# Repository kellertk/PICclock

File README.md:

# PICclock

Variable-frequency clock generator using PIC16F18344 hardware NCO.

See [src/README.md](src/README.md) and [hardware/README.md](hardware/README.md) for details.

## Features

- 1 Hz to 1 MHz output with 50% duty cycle
- Hardware NCO for 12+ Hz (zero CPU overhead)
- Software timing for 1-11 Hz
- Logarithmic frequency sweep via potentiometer
- Step mode for single pulses

## Building

1. Run the configure script:
   - Windows: `.\configure.ps1`
   - Linux/macOS: `./configure`

2. Build: `make`

3. Flash: `make flash`

## Requirements

- Microchip XC8 compiler
- MPLAB X IDE (for IPE and DFP)
- PICkit 5 (or compatible programmer)
- PIC16F1xxxx_DFP device family pack

## License

This project is intentionally available under a restrictive license: CC BY-NC-SA.
Commercial use of this work is not permitted without prior agreement. Please contact
me if you need alternate licensing terms. See [LICENSE.txt](LICENSE.txt) for details.

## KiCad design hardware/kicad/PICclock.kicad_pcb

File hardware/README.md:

# PICclock Hardware

## Overview

**Architecture:**
```
                          ACTIVE CLOCK OUTPUT
                                  ^
                                  |
                          +-------+-------+
                          |U3: EL7232CNZ  |
                          | Line Driver   |
                          +-------+-------+
                                  |
                          +-------+-------+
                          |U2: 74HC00     |
                          | (VAR/HS MUX)  |
                          +---+-------+---+
                              |       |
                +-------------+       +-------------+
                |                                   |
        VARIABLE CLOCK                        HIGH-SPEED
        (PIC RB6 NCO output)                  OSCILLATOR
                |                                (Y2)
          +-----+-----+
          |   PIC     |
          |   U1      |
          +-----+-----+
           |  |  |  |  |
       [POT][BTN][SW1][SW2]
```

**Clock Modes:**
- **Variable**: Hybrid NCO/software clock from PIC (1 Hz - 1 MHz), 50% duty cycle
- **Step**: Single pulse per button press (handled by PIC, debounced in software)
- **High-Speed**: External oscillator bypass

**Frequency Control:** PIC reads potentiometer via ADC. Hardware NCO generates clock for 12 Hz - 1 MHz; software timing handles 1 Hz - 11 Hz. Frequency accuracy inherits PIC crystal stability (typically ±50 ppm).

**Output Driver:** EL7232CNZ line driver buffers clock output.

**Variable Frequency Range:** 1 Hz to 1 MHz (hybrid NCO/software, 50% duty cycle)

---

## Components

### ICs

| Ref | Part | Function |
|-----|------|----------|
| U1 | PIC16F18344-I/P | Clock generation (NCO + software timing) |
| U2 | 74HC00 | Quad NAND (var/HS mux) |
| U3 | EL7232CNZ | Line driver |

### Oscillators

| Ref | Part | Function |
|-----|------|----------|
| Y1 | 24 MHz crystal | PIC clock |
| Y2 | Oscillator module (w/enable) | High-speed clock (user-selected frequency) |

### Switches & Controls

| Ref | Part | Function |
|-----|------|----------|
| SW1 | SPDT slide | Variable/Step select |
| SW2 | SPDT slide | Variable/High-Speed select |
| SW3 | Pushbutton (NO) | Step pulse trigger |
| VR1 | 10K pot | Frequency control |

### Passive Components

| Ref | Value | Function |
|-----|-------|----------|
| C1 | 10nF | U1 bypass |
| C2 | 100nF | U1 bypass |
| C3, C4 | 22pF | Y1 load caps |
| C5 | 10nF | U2 bypass |
| C6 | 100nF | U2 bypass |
| C7 | 10nF | U3 bypass |
| C8 | 100nF | U3 bypass |
| R1 | 10K | MCLR pull-up |
| R2 | 330Ω | Debug LED current limit |
| R3 | 47Ω | Clock output series resistor |
| R4 | 470Ω | Clock LED current limit |
| LED1 | LED | Debug indicator |
| LED2 | LED | Clock indicator |

---

## Signal Reference

| Signal | Description |
|--------|-------------|
| VAR_CLK | Variable clock from PIC (RB6 NCO1), active low |
| HS_CLK | High-speed external oscillator |
| STEP_SEL | Step mode select (SW1, active low = step) |
| HALT_SEL | High-speed mode select (SW2, active low = high-speed) |
| CLK_OUT | Final clock output (from U3) |

---

## U1: PIC16F18344-I/P (DIP-20)

```
                    +------------+
              VDD --|1         20|-- VSS (GND)
         RA5/OSC1 --|2         19|-- RA0/AN0 <-- VR1 (POT)
         RA4/OSC2 --|3         18|-- RA1/ICSPCLK
     MCLR/VPP/RA3 --|4         17|-- RA2 -x
DEBUG_LED <-- RC5 --|5         16|-- RC0 -x
      SW3 --> RC4 --|6         15|-- RC1 -x
      SW1 --> RC3 --|7         14|-- RC2 -x
      SW2 --> RC6 --|8         13|-- RB4 -x
           x- RC7 --|9         12|-- RB5 -x
           x- RB7 --|10        11|-- RB6 --> VAR_CLK
                    +------------+
```

| Pin | Name | Signal | To |
|-----|------|--------|----|  
| 1 | VDD | +5V | +5V, J1-2 |
| 2 | RA5/OSC1 | XTAL | Y1, C1 |
| 3 | RA4/OSC2 | XTAL | Y1, C2 |
| 4 | MCLR/VPP/RA3 | MCLR | +5V via R1, J1-1 |
| 5 | RC5 | DEBUG_LED | LED, current limit resistor to GND |
| 6 | RC4 | STEP_BTN | SW3 (internal pull-up) |
| 7 | RC3 | STEP_SEL | SW1 common |
| 8 | RC6 | HALT_SEL | SW2 common |
| 9 | RC7 | - | nc |
| 10 | RB7 | - | nc |
| 11 | RB6 | VAR_CLK | U2-4 (mux input) |
| 12 | RB5 | - | nc |
| 13 | RB4 | - | nc |
| 14 | RC2 | - | nc |
| 15 | RC1 | - | nc |
| 16 | RC0 | - | nc |
| 17 | RA2 | - | nc |
| 18 | RA1 | ICSPCLK | J1-5 |
| 19 | RA0/AN0 | POT | VR1 wiper, J1-4 (ICSPDAT) |
| 20 | VSS | GND | GND, J1-3 |

---

## U2: 74HC00

```
74HC00 (DIP-14)
       +-------+
    1A-|1    14|-VCC
    1B-|2    13|-4B
    1Y-|3    12|-4A
    2A-|4    11|-4Y
    2B-|5    10|-3B
    2Y-|6     9|-3A
   GND-|7     8|-3Y
       +-------+
```

| Pin | Signal | To |
|-----|--------|----|  
| 1 | 1A | SW2 |
| 2 | 1B | SW2 |
| 3 | 1Y | S̄ → U2-10 |
| 4 | 2A | VAR_CLK (from U1-11, PIC RB6) |
| 5 | 2B | SW2 |
| 6 | 2Y | U2-12 |
| 7 | GND | GND |
| 8 | 3Y | U2-13 |
| 9 | 3A | HS_CLK (from Y2-3) |
| 10 | 3B | U2-3 (S̄) |
| 11 | 4Y | MUX_OUT → U3-2 (line driver input) |

**Mux Truth Table:**

| SW2 | Output |
|-----|--------|
| GND (low) | HS_CLK (high-speed oscillator) |
| +5V (high) | VAR_CLK (PIC NCO/software clock or step pulse) |

---

## U3: EL7232CNZ Line Driver

Dual inverting line driver with 3-state outputs. Enable pins are active high.

```
EL7232CNZ (DIP-8)
        +-------+
    ENA-|1     8|-V+
   A IN-|2     7|-A OUT
    ENB-|3     6|-B OUT
   B IN-|4     5|-GND
        +-------+
```

| Pin | Signal | To |
|-----|--------|----|
| 1 | ENA | +5V (always enabled) |
| 2 | A IN | MUX_OUT (from U2-11), U3-4 |
| 3 | ENB | +5V (always enabled) |
| 4 | B IN | U3-2 (A IN) |
| 5 | GND | GND |
| 6 | B OUT | LED2 anode, R4 to GND |
| 7 | A OUT | R3 → J2-1 |
| 8 | V+ | +5V |

**Note:** Inverting driver. Channel A drives clock output. Channel B mirrors channel A to drive clock indicator LED.

## Y2: High-Speed Oscillator Module

Standard 4-pin metal can oscillator with active-low enable.

```
     +---------+
     |   Y2    |
     | OSC CAN |
     +---------+
      1  2  3  4
      |  |  |  |
    /EN GND OUT VCC
      |      |   |
     SW2   U2-9 +5V
```

| Pin | Signal | To |
|-----|--------|----|
| 1 | /EN | SW2 common (active low) |
| 2 | GND | GND |
| 3 | OUT | HS_CLK → U2-9 |
| 4 | VCC | +5V |

When SW2=GND (halt/HS mode): oscillator enabled, outputs HS_CLK.  
When SW2=+5V (run mode): oscillator disabled, PIC generates clock.

## SW1: SPDT Slide Switch (Variable/Step Select)

```
SW1 (Variable/Step):
  +5V ──[1]
           ├── STEP_SEL → U1-7 (PIC RC3)
  GND ──[2]
```

- **Position 1 (+5V):** Variable mode - PIC generates continuous clock based on pot
- **Position 2 (GND):** Step mode - PIC waits for button press, outputs single pulse

---

## SW2: SPDT Slide Switch (Variable/High-Speed Select)

```
SW2 (Var / High-Speed):
  +5V ──[1]
           ├──┬── HALT_SEL → U1-8 (PIC RC6)
  GND ──[2]   ├── SEL   → U2-1, U2-2, U2-5
              └── /EN   → Y2-1 (oscillator enable, active low)
```

- **Position 1 (+5V):** Variable/Step mode - PIC generates clock, Y2 disabled
- **Position 2 (GND):** High-speed mode - PIC halted, Y2 enabled

---

## SW3: Step Button

Normally-open momentary pushbutton. PIC internal pull-up enabled, debounced in software.

```
U1-6 (PIC RC4) ──┬── [SW3] ── GND
                  │
            (internal pull-up)
```

In step mode (SW1=low), pressing SW3 causes PIC to output a single clock pulse.

---

| 1 | MCLR/VPP | U1-4 (RA3), R1 to +5V |
| 2 | VDD | +5V |
| 3 | VSS | GND |
| 4 | ICSPDAT | U1-19 (RA0) |
| 5 | ICSPCLK | U1-18 (RA1) |

---

## J2: Clock Output (1x2)

| Pin | Signal | To |
|-----|--------|----|  
| 1 | CLK_OUT | R3 ← U3-7 (EL7232 A OUT) |

## BOM

### ICs
| Ref | Part | Package | Qty |
|-----|------|---------|-----|
| U1 | PIC16F18344-I/P | DIP-20 | 1 |
| U2 | 74HC00 | DIP-14 | 1 |
| U3 | EL7232CNZ | DIP-8 | 1 |
| U4 | LM3914 | DIP-18 | 1 |
| Q1 | 2N7000 | TO-92 | 1 |
| Y2 | Oscillator module | DIP-8/14 | 1 |

### Crystal & Capacitors
| Ref | Value | Qty | Function |
|-----|-------|-----|----------|
| Y1 | 24 MHz | 1 | PIC crystal |
| C1, C2 | 22pF | 2 | Y1 load caps |
| C3, C4, C5, C6 | 100nF | 4 | Decoupling |

### Resistors
| Ref | Value | Qty | Function |
|-----|-------|-----|----------|
| R1 | 10K | 1 | MCLR pull-up |

### Switches & Controls
| Ref | Part | Qty | Function |
|-----|------|-----|----------|
| VR1 | 10K pot | 1 | Frequency control |
| SW1 | SPDT slide | 1 | Var/Step select |
| SW2 | SPDT slide | 1 | (Var+Step)/HS select |
| SW3 | Pushbutton NO | 1 | Step trigger |

### Connectors
| Ref | Part | Qty | Function |
|-----|------|-----|----------|
| J1 | 1x5 header | 1 | ICSP |
| J2 | 1x2 header | 1 | Clock output |

---

## Data Flow

### Variable Clock Mode (SW1=+5V, SW2=+5V):
1. Y2 oscillator disabled (/EN=high)
2. PIC sees HALT_SEL=high on RC6, STEP_SEL=high on RC3
3. PIC reads potentiometer on AN0
4. PIC generates clock on RB6 using NCO (≥12 Hz) or software timing (<12 Hz)
5. U2 NAND mux passes VAR_CLK
6. U3 line driver buffers output
7. CLK_OUT = hybrid NCO/software clock (1 Hz to 1 MHz)

### Step Mode (SW1=GND, SW2=+5V):
1. Y2 oscillator disabled (/EN=high)
2. PIC sees HALT_SEL=high on RC6, STEP_SEL=low on RC3
3. PIC waits for button press on RC4 (debounced in software)
4. On press: PIC outputs single pulse on RB6
5. U2 mux passes pulse to output
6. CLK_OUT = single step pulse

### High-Speed Mode (SW2=GND):
1. Y2 oscillator enabled (/EN=low)
2. PIC sees HALT_SEL=low on RC6, holds RB6 low, LED off
3. U2 mux selects HS_CLK
4. U3 line driver buffers output
5. CLK_OUT = high-speed oscillator frequency
6. SW1 position ignored

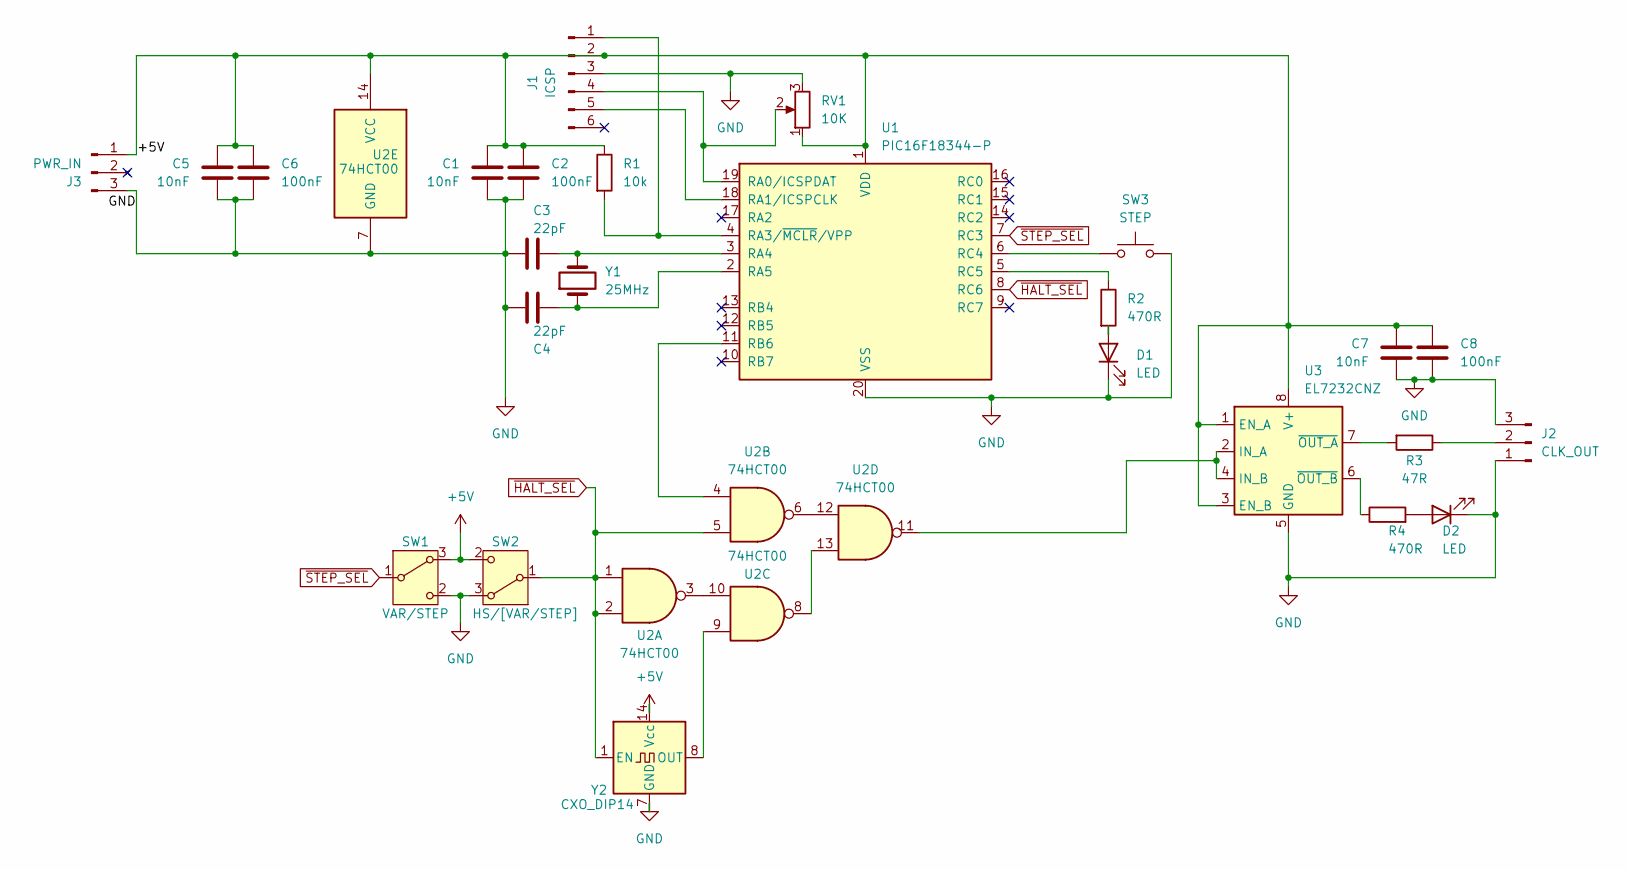
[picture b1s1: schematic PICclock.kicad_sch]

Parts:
C1, C5, C7: 10nF; C_Disc_D6.0mm_W2.5mm_P5.00mm
C2, C6, C8: 100nF; C_Disc_D6.0mm_W2.5mm_P5.00mm
C3, C4: 22pF; C_Disc_D6.0mm_W2.5mm_P5.00mm
D1, D2: LED; LED_D3.0mm_FlatTop
J1: ICSP; PinSocket_1x06_P2.54mm_Vertical
J2: CLK_OUT; PinHeader_1x03_P2.54mm_Vertical
J3: PWR_IN; PinHeader_1x03_P2.54mm_Vertical
R1: 10k; R_Axial_DIN0207_L6.3mm_D2.5mm_P10.16mm_Horizontal
R2, R4: 470R; R_Axial_DIN0207_L6.3mm_D2.5mm_P10.16mm_Horizontal
R3: 47R; R_Axial_DIN0207_L6.3mm_D2.5mm_P10.16mm_Horizontal
RV1: 10K; Potentiometer_Bourns_3339P_Vertical
SW1: VAR/STEP; SW_Slide-03_Wuerth-WS-SLTV_10x2.5x6.4_P2.54mm
SW2: HS/[VAR/STEP]; SW_Slide-03_Wuerth-WS-SLTV_10x2.5x6.4_P2.54mm
SW3: STEP; SW_Cherry_MX_1.00u_PCB
U1: PIC16F18344-P; DIP-20_W7.62mm_Socket_LongPads
U2: 74HCT00; DIP-14_W7.62mm_Socket_LongPads
U3: EL7232CNZ; DIP-8_W7.62mm_Socket_LongPads
Y1: 25MHz; Crystal_HC49-U_Vertical
Y2: CXO_DIP14; Oscillator_DIP-14_LargePads

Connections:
+5V: C1.2, C2.1, C5.2, C6.1, C7.2, C8.1, J1.2, J3.1, R1.1, RV1.1, SW1.3 (A), SW2.2 (C), U1.1 (VDD), U2.14 (VCC), U3.1 (EN_A), U3.3 (EN_B), U3.8 (V+), Y2.14 (Vcc)
GND: C1.1, C2.2, C3.1, C4.2, C5.1, C6.2, C7.1, C8.2, D1.1 (K), D2.1 (K), J1.3, J2.1, J2.3, J3.3, RV1.3, SW1.2 (C), SW2.3 (A), SW3.2, U1.20 (VSS), U2.7 (GND), U3.5 (GND), Y2.7 (GND)
unnamed: D1.2 (A), R2.2
unnamed: D2.2 (A), R4.2
unnamed: J1.1, R1.2, U1.4 (RA3/~MCLR/VPP)
unnamed: J1.4, RV1.2, U1.19 (RA0/ICSPDAT)
unnamed: J1.5, U1.18 (RA1/ICSPCLK)
unnamed: J2.2, R3.1
unnamed: C3.2, U1.3 (RA4), Y1.2
unnamed: C4.1, U1.2 (RA5), Y1.1
unnamed: U1.11 (RB6), U2.4
unnamed: SW3.1, U1.6 (RC4)
unnamed: R2.1, U1.5 (RC5)
unnamed: U2.3, U2.10
unnamed: U2.6, U2.12
unnamed: U2.8, U2.13
unnamed: U2.11, U3.2 (IN_A), U3.4 (IN_B)
unnamed: R3.2, U3.7 (~OUT_A)
unnamed: R4.1, U3.6 (~OUT_B)
unnamed: U2.9, Y2.8 (OUT)
~HALT_SEL: SW2.1 (B), U1.8 (RC6), U2.1, U2.2, U2.5, Y2.1 (EN)
~STEP_SEL: SW1.1 (B), U1.7 (RC3)

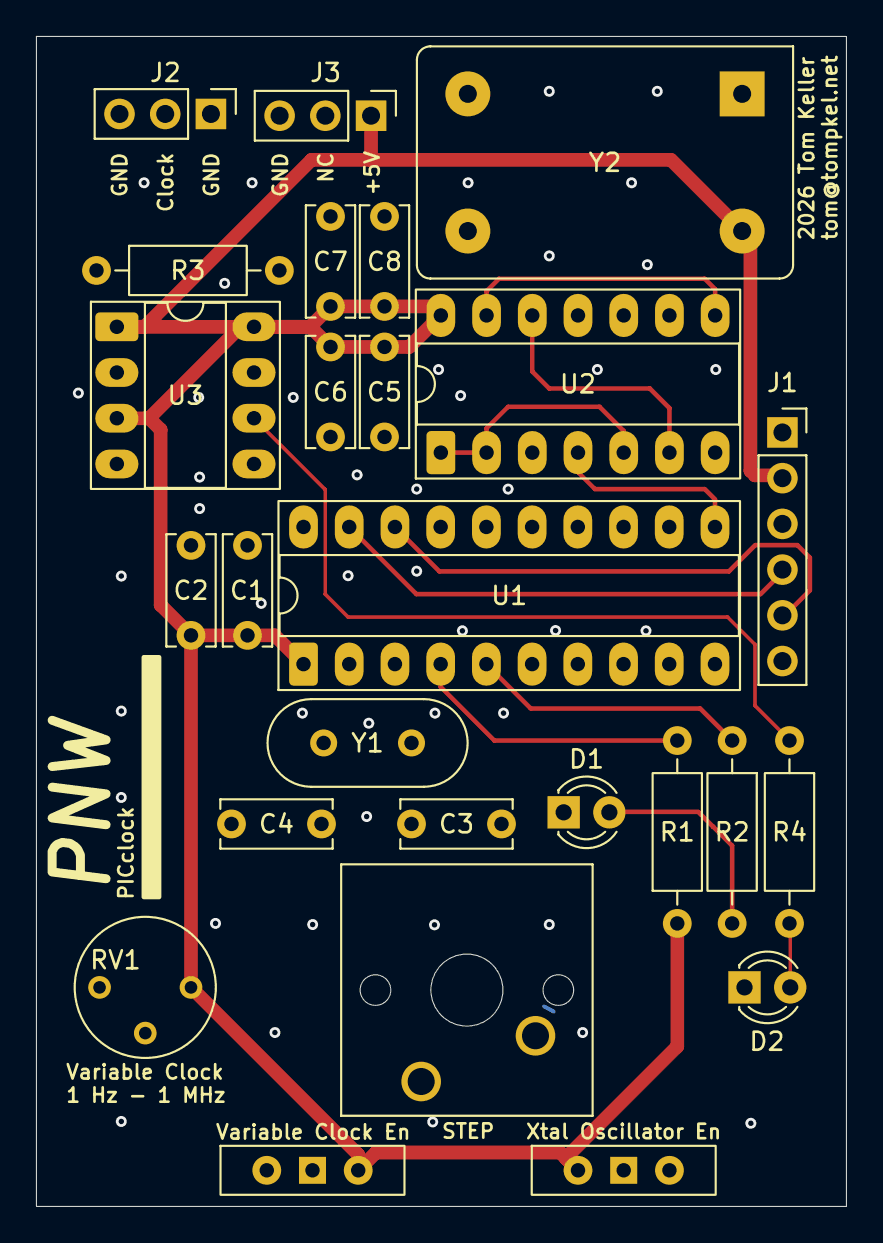
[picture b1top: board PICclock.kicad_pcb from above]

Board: 4 copper layers, 45.0 x 65.0 mm, 26 parts (0 on the bottom side), 22 nets.

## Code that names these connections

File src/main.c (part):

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#pragma config CLKOUTEN = OFF  // Clock out disabled
#pragma config CSWEN = OFF     // Clock switch disabled
#pragma config FCMEN = OFF     // Fail-safe clock monitor disabled
#pragma config MCLRE = ON      // MCLR pin enabled (RA3)
#pragma config PWRTE = OFF     // Power-up timer disabled
#pragma config WDTE = OFF      // Watchdog disabled
#pragma config LPBOREN = OFF   // Low-power BOR disabled
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
#define _XTAL_FREQ 24000000UL  // 24 MHz external crystal

// Pin 2:  RA5/OSC1 = Crystal
// Pin 3:  RA4/OSC2 = Crystal
// Pin 4:  RA3/MCLR = Reset
// Pin 5:  RC5 = Debug LED output
// Pin 6:  RC4 = Step button (SW3, active low)
// Pin 7:  RC6 = Halt select (SW2, active low)
// Pin 8:  RC3 = Step mode select (SW1, active low)
// Pin 11: RB6 = NCO1 output (drives EL7232CNZ)
// Pin 19: RA0 = ADC input (pot)

#define DEBUG_LED   LATCbits.LATC5   // Debug LED (active high)
#define HALT_SEL    PORTCbits.RC6    // Halt select (SW2)
#define STEP_BTN    CLCDATAbits.MLC1OUT  // Step button (SW3) - HW debounced via 3-CLC
#define STEP_SEL    PORTCbits.RC3    // Step mode select (SW1)

static void adc_init(void) {
    ADCON0 = 0x01;         // AN0 selected, ADC enabled
    ADCON1 = 0x60;         // Left-justified, Fosc/64, Vref = VDD/VSS
    ANSELAbits.ANSA0 = 1;  // RA0 is analog
}

static uint8_t adc_read(void) {
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    TRISBbits.TRISB6 = 0;       // Output
    ANSELBbits.ANSB6 = 0;       // Digital
    
    // Route NCO1 to RB6 via PPS (Peripheral Pin Select)
    RB6PPS = 0x1D;              // NCO1 output (0x1D per datasheet Table 13-3)
    
    NCO1CON = 0x00;             // Disable NCO while configuring
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
/**
 * Disconnect NCO from pin (for software mode)
 * Sets RB6 as regular GPIO output
 */
static void nco_disconnect(void) {
    NCO1CON = 0x00;
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void main(void) {
    // Configure I/O
    // PORTA: RA0=analog in, RA4/RA5=crystal
    TRISA = 0b00110001;         // RA0,RA4,RA5 input (crystal pins), rest output
    ANSELA = 0b00000001;        // Only RA0 is analog
    LATA = 0x00;
    
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
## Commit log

2026-01-23 move readme files
2026-01-23 update design rules for 4-layer
2026-01-23 update VAR_CLOCK to active low
2026-01-24 add additional via stitching
2026-01-24 fix license text
2026-01-31 add power input
2026-02-09 switch to CLC for debounce
